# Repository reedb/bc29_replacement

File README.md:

# bc29_replacement
Replacement PCB for BC29 AH Meter

To do:
1. Board physical dimensions, use original packaging.
2. MCU use msp430i2041
3. Input filter with common mode choke
4. Current input network
5. Voltage input network
6. 20-pin output connector, verify orientation
7. PSU

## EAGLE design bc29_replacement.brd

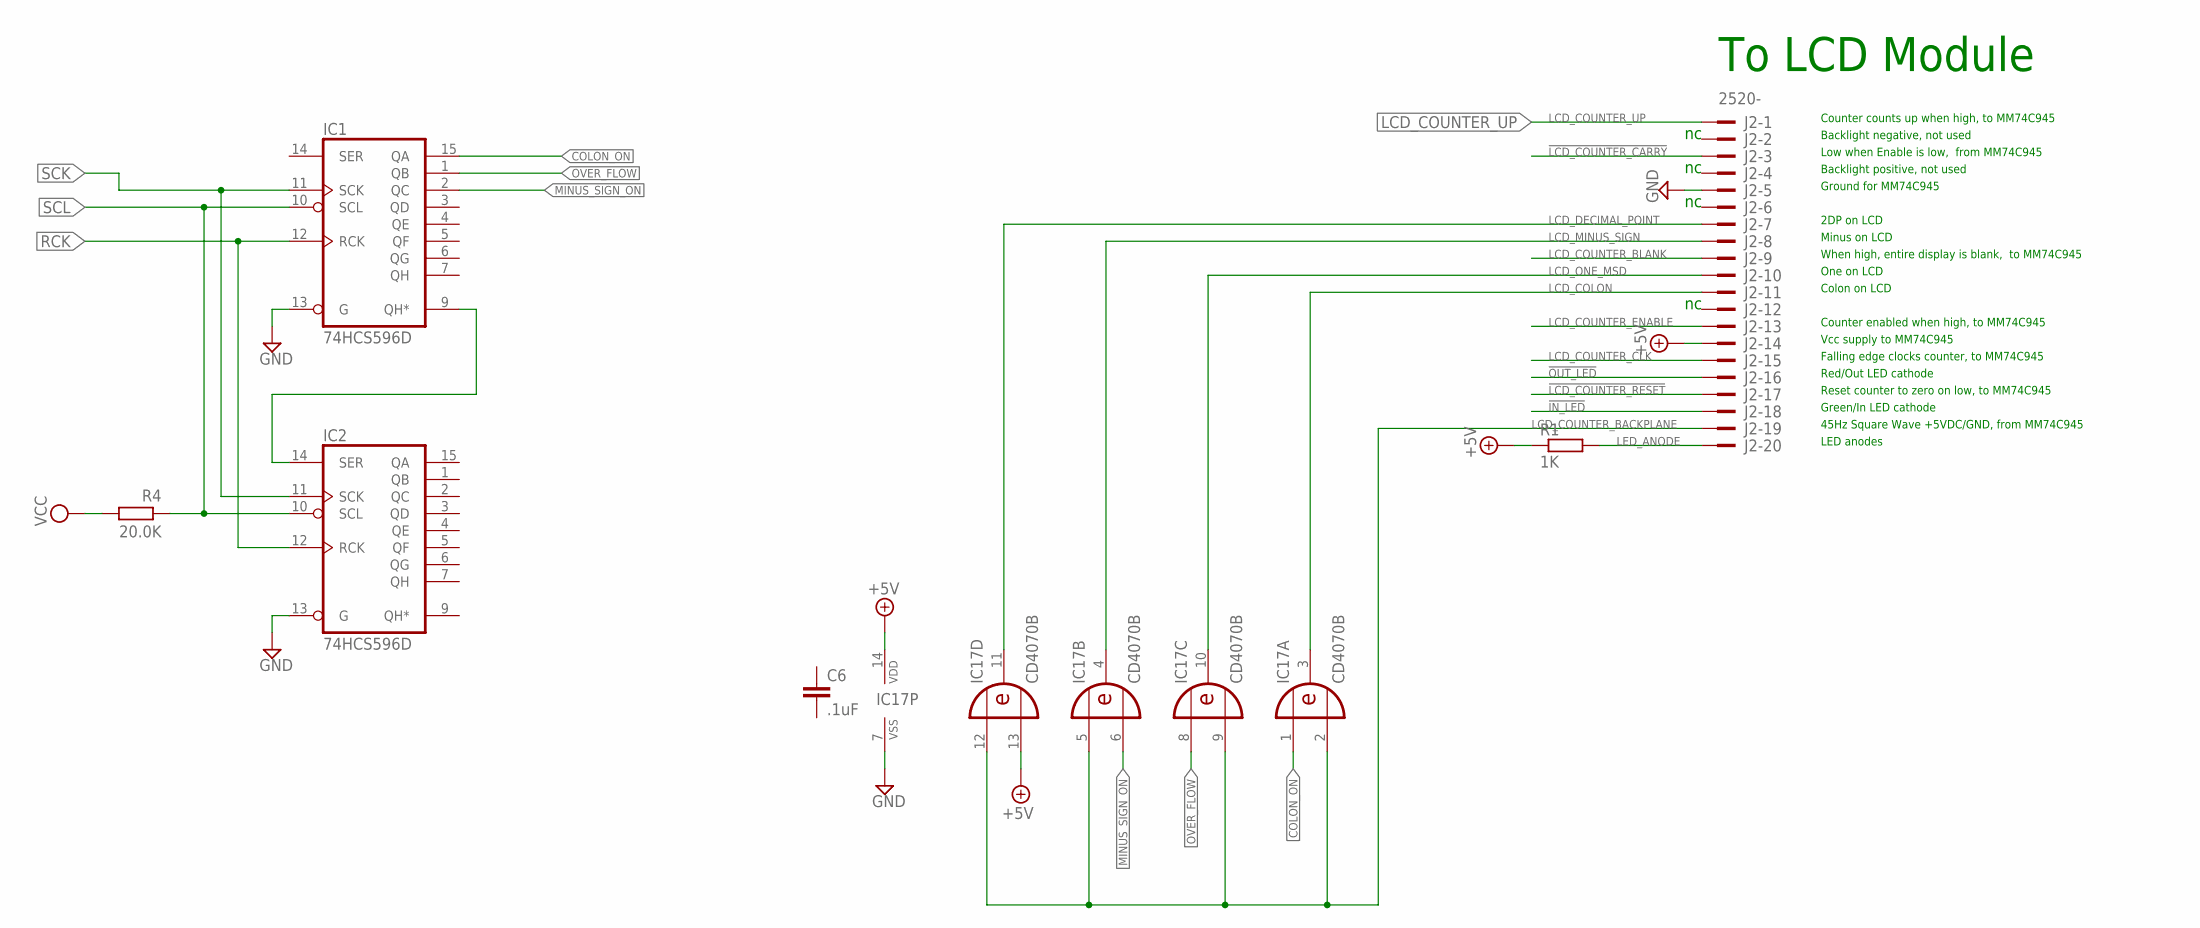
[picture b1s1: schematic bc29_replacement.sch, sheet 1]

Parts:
C6: .1uF; C0805
IC1, IC2: 74HCS596D; SO16
IC17: CD4070B; SO14
J2: 2520-; PAK100/2500-20
R1: 1K; R0805
R4: 20.0K; R0805

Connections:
!IN_LED: J2.18
!LCD_COUNTER_CARRY: J2.3
!LCD_COUNTER_RESET: J2.17
!OUT_LED: J2.16
+5V: IC17.13 (I1), J2.14, R1.1; also elsewhere on the board
+12V: IC17.14 (VDD)
COLON_ON: IC17.1 (I0)
GND: IC1.8 (GND), IC1.13 (G), IC2.8 (GND), IC2.13 (G), IC17.7 (VSS), J2.5; also elsewhere on the board
LCD_COLON: IC17.3 (O), J2.11
LCD_COUNTER_BACKPLANE: IC17.2 (I1), IC17.5 (I0), IC17.9 (I1), IC17.12 (I0), J2.19
LCD_COUNTER_BLANK: J2.9
LCD_COUNTER_CLK: J2.15
LCD_COUNTER_ENABLE: J2.13
LCD_COUNTER_UP: J2.1
LCD_DECIMAL_POINT: IC17.11 (O), J2.7
LCD_MINUS_SIGN: IC17.4 (O), J2.8
LCD_ONE_MSD: IC17.10 (O), J2.10
LED_ANODE: J2.20, R1.2
MINUS_SIGN_ON: IC17.6 (I1)
unnamed: IC1.9 (QH*), IC2.14 (SER)
OVER_FLOW: IC17.8 (I0)
RCK: IC1.12 (RCK), IC2.12 (RCK)
SCK: IC1.11 (SCK), IC2.11 (SCK)
SCL: IC1.10 (SCL), IC2.10 (SCL), R4.1
VCC: IC1.16 (VCC), IC2.16 (VCC), R4.2; also elsewhere on the board

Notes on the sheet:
To LCD Module
45Hz Square Wave +5VDC/GND, from MM74C945
Reset counter to zero on low, to MM74C945
Green/In LED cathode
Red/Out LED cathode
LED anodes
Falling edge clocks counter, to MM74C945
Counter enabled when high, to MM74C945
Counter counts up when high, to MM74C945
Low when Enable is low, from MM74C945
When high, entire display is blank, to MM74C945
2DP on LCD
Minus on LCD
One on LCD
Colon on LCD
Vcc supply to MM74C945
Backlight positive, not used
Backlight negative, not used
Ground for MM74C945

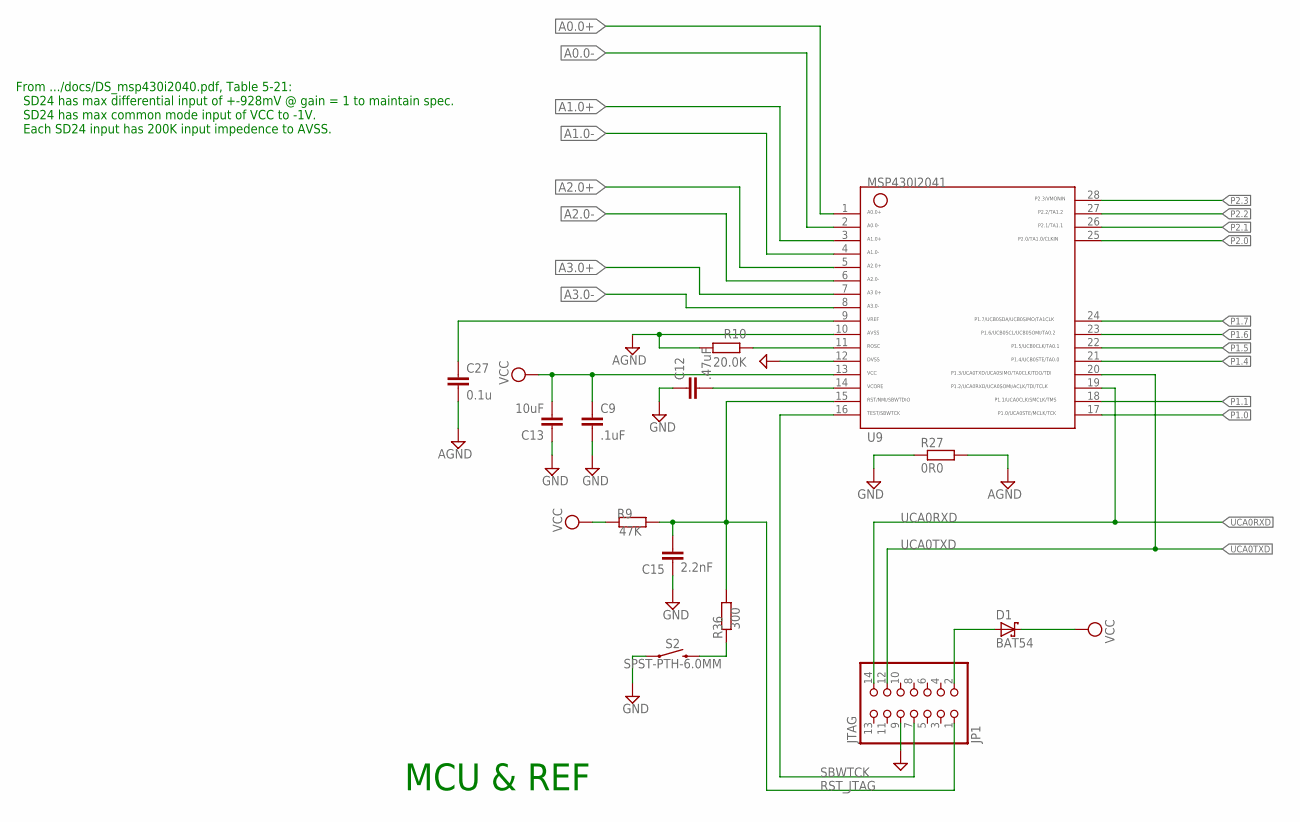
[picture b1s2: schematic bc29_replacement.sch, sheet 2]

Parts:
C9: .1uF; C0805
C12: .47uF; C0805
C13: 10uF; C0805
C15: 2.2nF; C0805
C27: 0.1u; 0805
D1: BAT54; SOT23
JP1: JTAG; 2X07
R9: 47K; R0805
R10: 20.0K; R0805
R27: 0R0; R0805
R36: 300; R0805
S2: SPST-PTH-6.0MM; TACTILE_SWITCH_PTH_6.0MM
U9: MSP430I2041TPW; PW28

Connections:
A0.0+: U9.1; also elsewhere on the board
A0.0-: U9.2; also elsewhere on the board
A1.0+: U9.3
A1.0-: U9.4
A2.0+: U9.5
A2.0-: U9.6
A3.0+: U9.7
A3.0-: U9.8
AGND: C27.2, R10.2, R27.2, U9.10
GND: C9.2, C12.1, C13.1, C15.1, JP1.9, R27.1, S2.1, U9.12; also elsewhere on the board
P1.0: U9.17
P1.1: U9.18
P1.4: U9.21
P1.5: U9.22
P1.6: U9.23
P1.7: U9.24
P2.0: U9.25
P2.1: U9.26
P2.2: U9.27
P2.3: U9.28
ROSC: R10.1, U9.11
RST_JTAG: C15.2, JP1.1, R9.1, R36.1, U9.15
RST_PB: R36.2, S2.3 (2)
SBWTCK: JP1.7, U9.16
UCA0RXD: JP1.14, U9.19
UCA0TXD: JP1.12, U9.20
VCC: C9.1, C13.2, D1.3 (C), R9.2, U9.13; also elsewhere on the board
VCC_JTAG: D1.1 (A), JP1.2
VCORE: C12.2, U9.14
VREF: C27.1, U9.9

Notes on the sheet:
MCU & REF
From .../docs/DS_msp430i2040.pdf, Table 5-21: SD24 has max differential input of +-928mV @ gain = 1 to maintain spec. SD24 has max common mode input of VCC to -1V. Each SD24 input has 200K input impedence to AVSS.

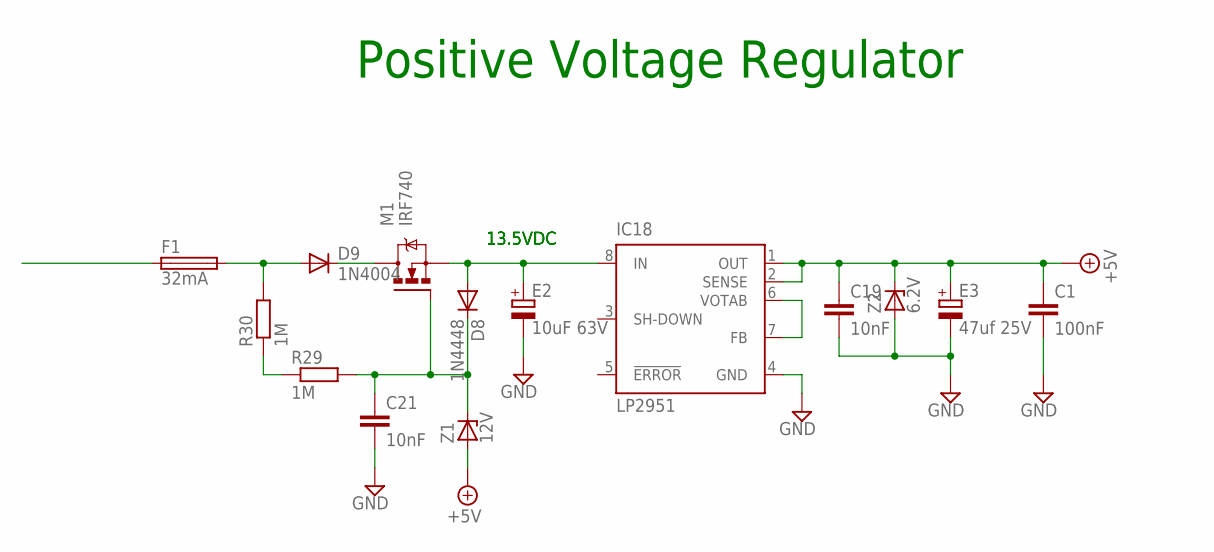
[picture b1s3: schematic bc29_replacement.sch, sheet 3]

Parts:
C1: 100nF; C1206
C19, C21: 10nF; C0805
D8: 1N4448; MINIMELF
D9: 1N4004; SOD80C
E2: 10uF 63V; E2,5-5
E3: 47uf 25V; E2,5-5
F1: 32mA; FUSE_HOLDER_5X20MM
IC18: LP2951; SO08
M1: IRF740; TO220BV
R29, R30: 1M; M0805
Z1: 12V; SOD80C
Z2: 6.2V; SOD80C

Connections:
13V5: D8.A, E2.+, IC18.8 (IN), M1.S
+5V: C1.1, C19.1, E3.+, IC18.1 (OUT), IC18.2 (SENSE), Z1.A, Z2.C; also elsewhere on the board
+BATT_FILT: F1.1; also elsewhere on the board
DRAIN: D9.C, M1.D
FUSED_BATT+: D9.A, F1.2, R30.2
GATE: C21.1, D8.C, M1.G, R29.2, Z1.C
GND: C1.2, C19.2, C21.2, E2.-, E3.-, IC18.4 (GND), Z2.A; also elsewhere on the board
unnamed: R29.1, R30.1
unnamed: IC18.6 (VOTAB), IC18.7 (FB)

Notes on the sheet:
13.5VDC
Positive Voltage Regulator

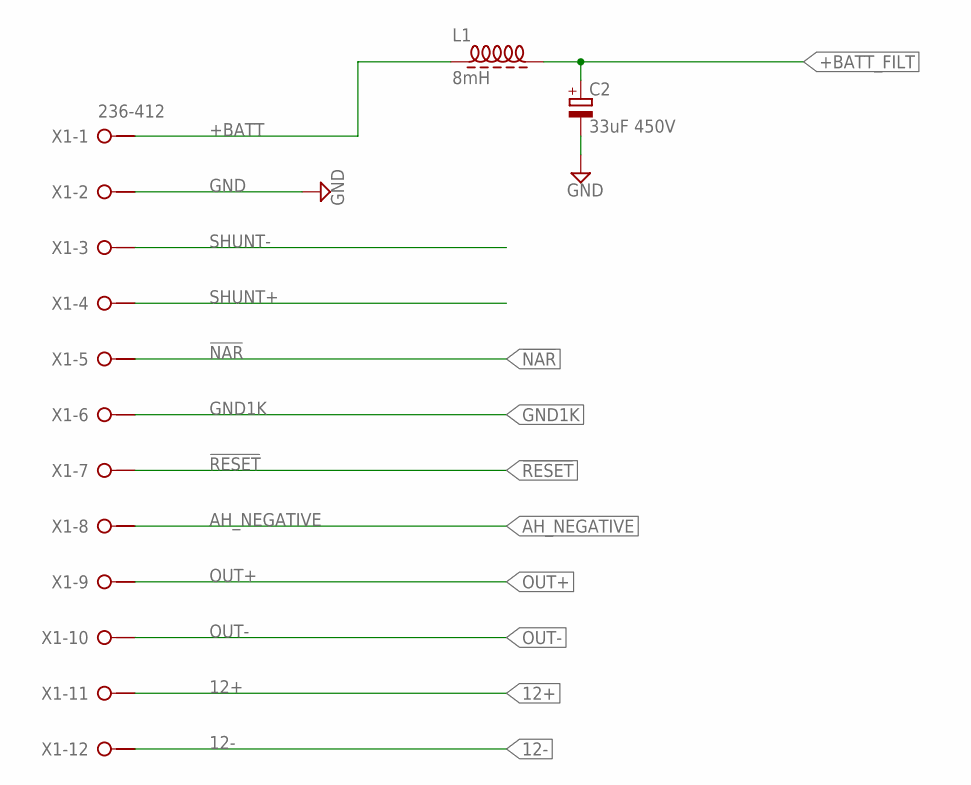
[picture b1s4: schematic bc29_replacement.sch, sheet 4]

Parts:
C2: 33uF 450V; E7,5-18
L1: 8mH; Z15/4
X1: 236-412

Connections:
12+: X1.11@1 (KL1)
12-: X1.12@1 (KL1)
!NAR: X1.5@1 (KL1)
!RESET: X1.7@1 (KL1)
+BATT: L1.1, X1.1@1 (KL1)
+BATT_FILT: C2.+, L1.2; also elsewhere on the board
AH_NEGATIVE: X1.8@1 (KL1)
GND: C2.-, X1.2@1 (KL1); also elsewhere on the board
GND1K: X1.6@1 (KL1)
OUT+: X1.9@1 (KL1)
OUT-: X1.10@1 (KL1)
SHUNT+: X1.4@1 (KL1)
SHUNT-: X1.3@1 (KL1)

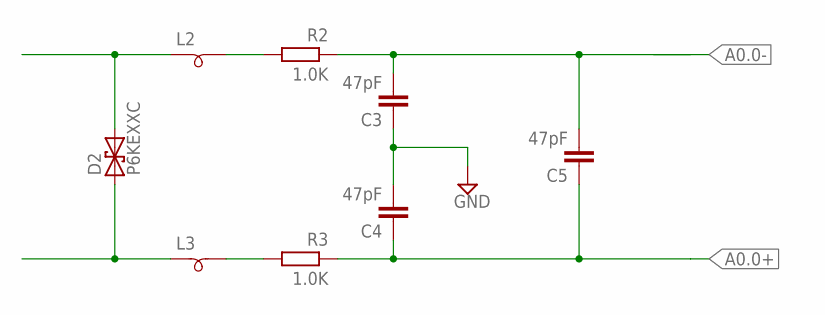
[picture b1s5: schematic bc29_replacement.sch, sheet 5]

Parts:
C3, C4, C5: 47pF; C0805
D2: P6KEXXC; CB417-15
L2, L3: SM-B9
R2, R3: 1.0K; R0805

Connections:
A0.0+: C4.1, C5.1, R3.1; also elsewhere on the board
A0.0-: C3.2, C5.2, R2.1; also elsewhere on the board
GND: C3.1, C4.2; also elsewhere on the board
unnamed: D2.C (2), L2.1
unnamed: D2.A (1), L3.1
unnamed: L2.2, R2.2
unnamed: L3.2, R3.2

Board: 2 copper layers, 45 parts (0 on the bottom side), 37 nets, no tracks yet.

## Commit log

2022-06-21 remove spurious datasheets
2022-06-21 MCU and PCB dimensions
2022-06-22 input network
2022-06-28 io expansion
2022-07-26 power
2022-08-13 add shift register

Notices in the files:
parts and their libraries:
SparkFun-Capacitors: Licensing: Creative Commons ShareAlike 4.0 International - https://creativecommons.org/licenses/by-sa/4.0
